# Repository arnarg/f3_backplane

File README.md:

# F3 Backplane

> F2 + 1 = F3, right?

This is a custom backplane PCB for Terramaster F2-221, which adds a socket for an NVMe SSD for booting an operating system from.

Blog post about creating this: https://codedbearder.com/posts/f3-backplane/

## Ordering from JLCPCB

The gerber zip file can be found under `fab/v1.0/f3_backplane.zip` and is generated for JLCPCB. When ordering the PCB make sure to select impedance controlled stackup ***JLC04161H-7628***.

Also, make sure to select ***Gold Fingers*** and ***30°finger chamfered***. It will recommend selecting an ENIG surface finish in order to get them _actually_ gold plated, but as this is more expensive and the backplane _shouldn't_ get removed and inserted into the motherboard often I just went with the standard HASL (with lead) surface finish and I haven't had any problems.

[Bill of materials](./f3_backplane.csv)

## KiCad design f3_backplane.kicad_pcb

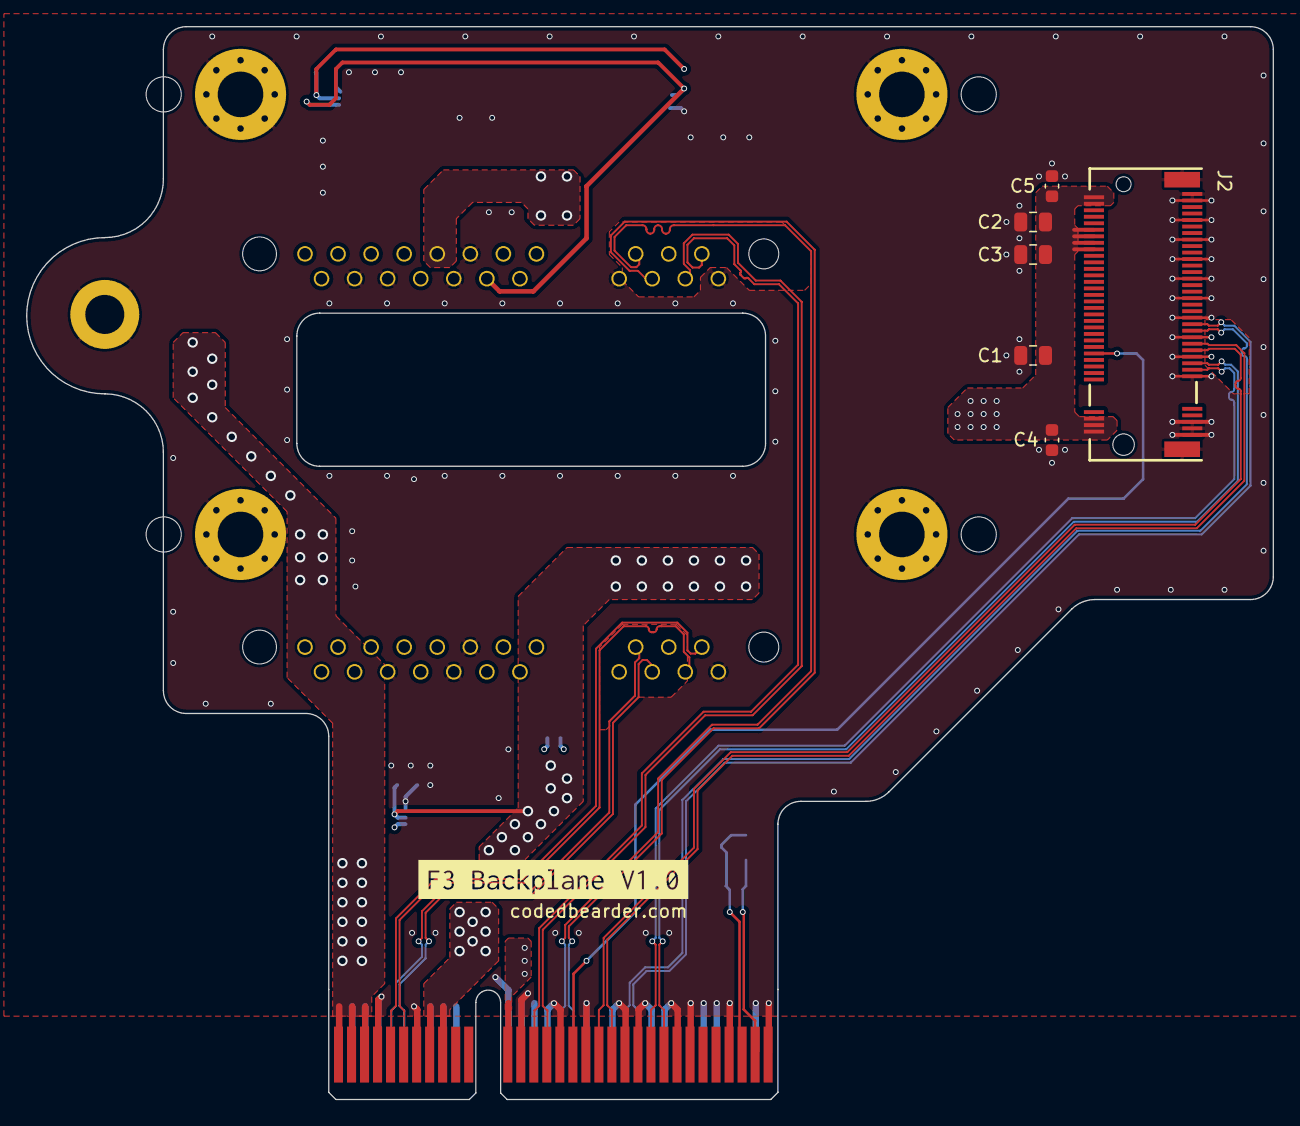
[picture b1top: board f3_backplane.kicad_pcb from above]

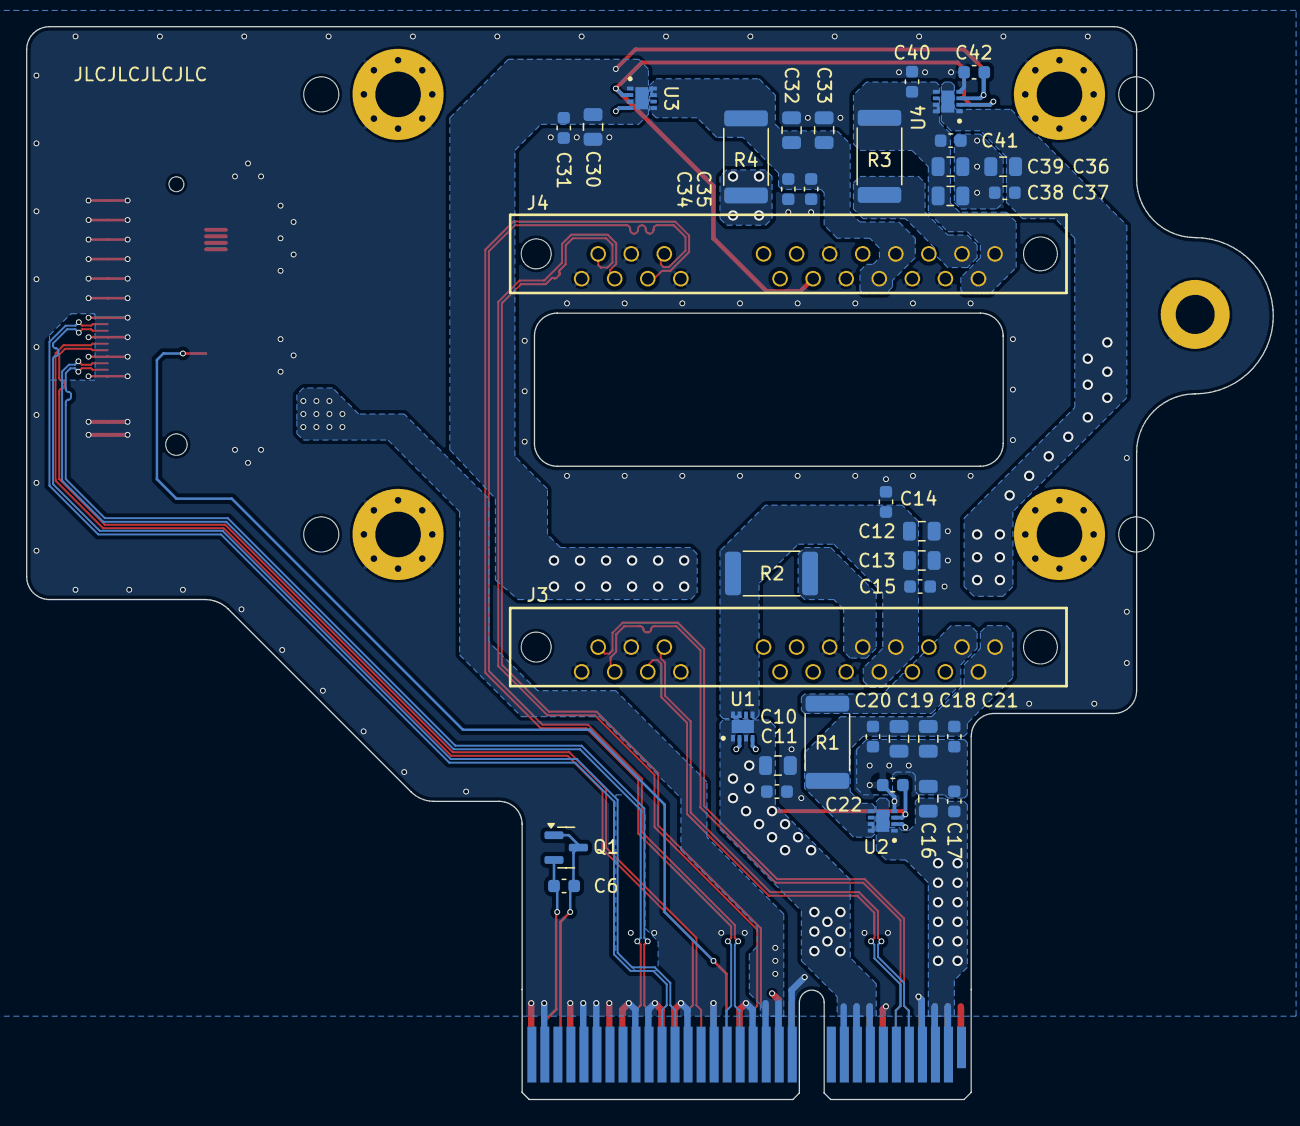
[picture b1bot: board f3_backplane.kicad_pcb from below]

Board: 4 copper layers, 95.8 x 82.4 mm, 49 parts (38 on the bottom side), 31 nets.

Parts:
C1, C2: 47u; C_0805_2012Metric
C3: 22u; C_0805_2012Metric
C4, C5: 100n; C_0603_1608Metric
C6, C11, C14, C15, C17, C20, C21, C22, C31, C34, C35, C37, C40, C41, C42: 100nF; C_0603_1608Metric
C10, C16, C30, C36: 10uF; C_0805_2012Metric
C12, C13, C18, C19, C32, C33, C38, C39: 22uF; C_0805_2012Metric
H1, H2, H3, H4: MountingHole_Pad; MountingHole_3.5mm_Pad_Via_With_Alignment_Hole
J1: PCIEx4_HOST
J2: Bus_M.2_Socket_M; Amphenol_MDT420M01001
J3, J4: SATA_Backplane; Molex_0877011001
Q1: MMBT3904; SOT-23
R1, R2, R3, R4: 2R2; R_2512_6332Metric
U1, U2, U3, U4: NCP45521

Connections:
+3.3V: C1.1, C2.1, C3.1, C4.1, C5.1, J1.A13 (3.3V), J1.A14 (3.3V), J1.B12 (3.3V), J2.2 (3.3V), J2.4 (3.3V), J2.12 (3.3V), J2.14 (3.3V), J2.16 (3.3V), J2.18 (3.3V), J2.70 (3.3V), J2.72 (3.3V), J2.74 (3.3V)
+5V: C10.1, C11.1, C22.1, C30.1, C31.1, C42.1, J1.A8 (5V), J1.A9 (5V), J1.A10 (5V), J1.B8 (5V), J1.B9 (5V), U1.1 (VIN), U1.3 (VCC), U1.9 (VIN), U2.3 (VCC), U3.1 (VIN), U3.3 (VCC), U3.9 (VIN), U4.3 (VCC)
+12V: C16.1, C17.1, C36.1, C37.1, J1.A2 (12V), J1.A3 (12V), J1.B1 (12V), J1.B2 (12V), J1.B3 (12V), U2.1 (VIN), U2.9 (VIN), U4.1 (VIN), U4.9 (VIN)
/Connector/B30: C6.1, J1.B30, Q1.1 (B), Q1.3 (C)
/Connector/B31: C6.2, J1.B31, Q1.2 (E)
/PCIE_REFCLK+: J1.B23 (PE1_REFCLK+), J2.55 (REFCLKp)
/PCIE_REFCLK-: J1.B24 (PE1_REFCLK-), J2.53 (REFCLKn)
/PCIE_RX+: J1.A21 (PE1_RX+), J2.43 (PERp0/SATA-B-)
/PCIE_RX-: J1.A22 (PE1_RX-), J2.41 (PERn0/SATA-B+)
/PCIE_TX+: J1.B19 (PE1_TX+), J2.49 (PETp0/SATA-A+)
/PCIE_TX-: J1.B20 (PE1_TX-), J2.47 (PETn0/SATA-A-)
/PERST#: J1.B17 (PERST), J2.50 (~PERST)
/SATA1/PRESENT#: J3.P4 (PRESENT#), U1.2 (EN), U2.2 (EN)
/SATA1/SATA_5V: C12.1, C13.1, C14.1, C15.1, J3.P8 (5V), J3.P9 (5V), R2.1, U1.5 (BLEED), U1.7 (VOUT)
/SATA1/SATA_12V: C18.1, C19.1, C20.1, C21.1, J3.P14 (12V), J3.P15 (12V), R1.1, U2.5 (BLEED), U2.7 (VOUT)
/SATA1/SATA_PRE_5V: J3.P7 (5V_PRE), R2.2
/SATA1/SATA_PRE_12V: J3.P13 (12V_PRE), R1.2
/SATA1_A+: J1.B5 (SATA1_A+), J3.S2 (SATA_A+)
/SATA1_A-: J1.B6 (SATA1_A-), J3.S3 (SATA_A-)
/SATA1_B+: J1.A5 (SATA1_B+), J3.S6 (SATA_B+)
/SATA1_B-: J1.A6 (SATA1_B-), J3.S5 (SATA_B-)
/SATA2/PRESENT#: J4.P4 (PRESENT#), U3.2 (EN), U4.2 (EN)
/SATA2/SATA_5V: C32.1, C33.1, C34.1, C35.1, J4.P8 (5V), J4.P9 (5V), R4.1, U3.5 (BLEED), U3.7 (VOUT)
/SATA2/SATA_12V: C38.1, C39.1, C40.1, C41.1, J4.P14 (12V), J4.P15 (12V), R3.1, U4.5 (BLEED), U4.7 (VOUT)
/SATA2/SATA_PRE_5V: J4.P7 (5V_PRE), R4.2
/SATA2/SATA_PRE_12V: J4.P13 (12V_PRE), R3.2
/SATA2_A+: J1.B14 (SATA2_A+), J4.S2 (SATA_A+)
/SATA2_A-: J1.B15 (SATA2_A-), J4.S3 (SATA_A-)
/SATA2_B+: J1.A16 (SATA2_B+), J4.S6 (SATA_B+)
/SATA2_B-: J1.A17 (SATA2_B-), J4.S5 (SATA_B-)
GND: C1.2, C2.2, C3.2, C4.2, C5.2, C10.2, C11.2, C12.2, C13.2, C14.2, C15.2, C16.2, C17.2, C18.2, C19.2, C20.2, C21.2, C22.2, C30.2, C31.2, C32.2, C33.2, C34.2, C35.2, C36.2, C37.2, C38.2, C39.2, C40.2, C41.2, C42.2, H1.1, H2.1, H3.1, H4.1, J1.A4 (GND), J1.A12 (GND), J1.A15 (GND), J1.A18 (GND), J1.A20 (GND), J1.A23 (GND), J1.A24 (GND), J1.A27 (GND), J1.A28 (GND), J1.A31 (GND), J1.B4 (GND), J1.B7 (GND), J1.B13 (GND), J1.B16 (GND), J1.B18 (GND), J1.B21 (GND), J1.B22 (GND), J1.B25 (GND), J1.B26 (GND), J1.B29 (GND), J1.B32 (GND), J2.1 (GND), J2.3 (GND), J2.9 (GND), J2.15 (GND), J2.21 (GND), J2.27 (GND), J2.33 (GND), J2.39 (GND), J2.45 (GND), J2.51 (GND), J2.57 (GND), J2.71 (GND), J2.73 (GND), J2.75 (GND), J3.P5 (GND), J3.P6 (GND), J3.P10 (GND), J3.P12 (GND), J3.S1 (GND), J3.S4 (GND), J3.S7 (GND), J4.P5 (GND), J4.P6 (GND), J4.P10 (GND), J4.P12 (GND), J4.S1 (GND), J4.S4 (GND), J4.S7 (GND), U1.4 (GND), U2.4 (GND), U3.4 (GND), U4.4 (GND)

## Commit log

2024-04-06 More routing
2024-04-07 Routing power
2024-04-07 Add ground plane to outer layers
2024-04-08 Finish v1.0
2024-04-26 Add thermal reliefs to internal ground plane
2024-04-26 Add README
2024-04-29 Add datasheet links and digikey part numbers
2024-04-29 Generate bill of materials
2024-04-29 Add info about ordering from JLCPCB
2024-04-29 Add README link to bill of materials
2024-04-29 Fix capacitor values
2024-04-30 Remove edge connector from bill of materials
2024-05-03 Improve differential pair intra-pair matching
2024-05-04 Create LICENSE
